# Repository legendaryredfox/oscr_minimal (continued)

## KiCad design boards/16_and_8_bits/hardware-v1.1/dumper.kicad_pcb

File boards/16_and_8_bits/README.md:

# 16_and_8_bits — placa de 5 slots

**README por versão** (renders de cima e de baixo, peças, diferenças): [v1.0](hardware-v1.0/README.md), [v1.1](hardware-v1.1/README.md).

**Slots:** SNES (62p), NES (72p), Famicom (60p), Mega Drive (64p) e GBA (32p, SMD, 3,3 V). Um cartucho por vez.

**Versões (regra do usuário: v1.0 = a mínima que funciona, com fusível; outras versões = mais recursos):**

- **v1.0** (144,1 × 118,1 mm): a mínima, com o fusível F1 (D144).
- **v1.1** (144,1 × 134,1 mm): a v1.0 mais o **seletor de tensão 3,3 V/5 V** nos slots **NES, Famicom e Mega Drive** (LDO LD1117V33 U4, Q1 de bypass, Q2 de comando pelo D18, R3 a R5, C10, C11) e o J1 "TRAVA 3,3 V" (D157, D138, D147). **O SNES fica sempre em 5 V** (o SA-1 não funciona a 3,3 V), assim como o PIC e o Si5351; o GBA tem o regulador U3. Firmware: ambiente `SerialASCII_Volt`.

**Estado:** DRC 0 erros nas duas versões (só os 4 avisos de biblioteca do furo M3), netlist confere com `docs/pinmap.md`, gerbers v1.0 e v1.1 em `fab/` (`fab/PEDIDO.md`). A v1.1 foi roteada pelo Freerouting: **revisar o layout no KiCad antes de encomendar**. Nada encomendado nem montado.

| Pasta | Conteúdo |
|---|---|
| `hardware-v1.0/`, `hardware-v1.1/` | `dumper.kicad_pro/_sch/_pcb` (KiCad 10) |
| `fab/` | `gerbers-<versão>/`, `bom-<versão>.csv`, `dumper-<versão>-jlcpcb.zip`, `PEDIDO.md` |
| `docs/` | `pinmap.md` (fonte da verdade), `bom.md`, `montagem.md` |

Verificação (da raiz do repositório):

```
python3 tools/check_netlist.py --board 16_and_8_bits boards/16_and_8_bits/hardware-v1.1/dumper.kicad_sch
kicad-cli sch erc boards/16_and_8_bits/hardware-v1.1/dumper.kicad_sch
kicad-cli pcb drc boards/16_and_8_bits/hardware-v1.1/dumper.kicad_pcb
tools/export_fab.sh 16_and_8_bits v1.1
```

**Peças opcionais:** o que se perde ao retirar cada componente, e que jogos são afetados, está em [`docs/bom.md`](docs/bom.md).

## Versões

Só a **v1.0** (`hardware-v1.0/`; fábrica em `fab/gerbers-v1.0/`, `fab/dumper-v1.0-jlcpcb.zip`, `fab/bom-v1.0.csv`; renders em `hardware-v1.0/render-cima.png` e `render-baixo.png`). Ela já leva o suporte do fusível F1 (D138). O 5V dos slots vai direto do Mega e **não é cortado por software** (o bloco de troca de cartucho, D126 a D128, foi retirado em D139): para trocar o cartucho, desligue o USB. Verificação: `python3 tools/check_netlist.py --board 16_and_8_bits`.

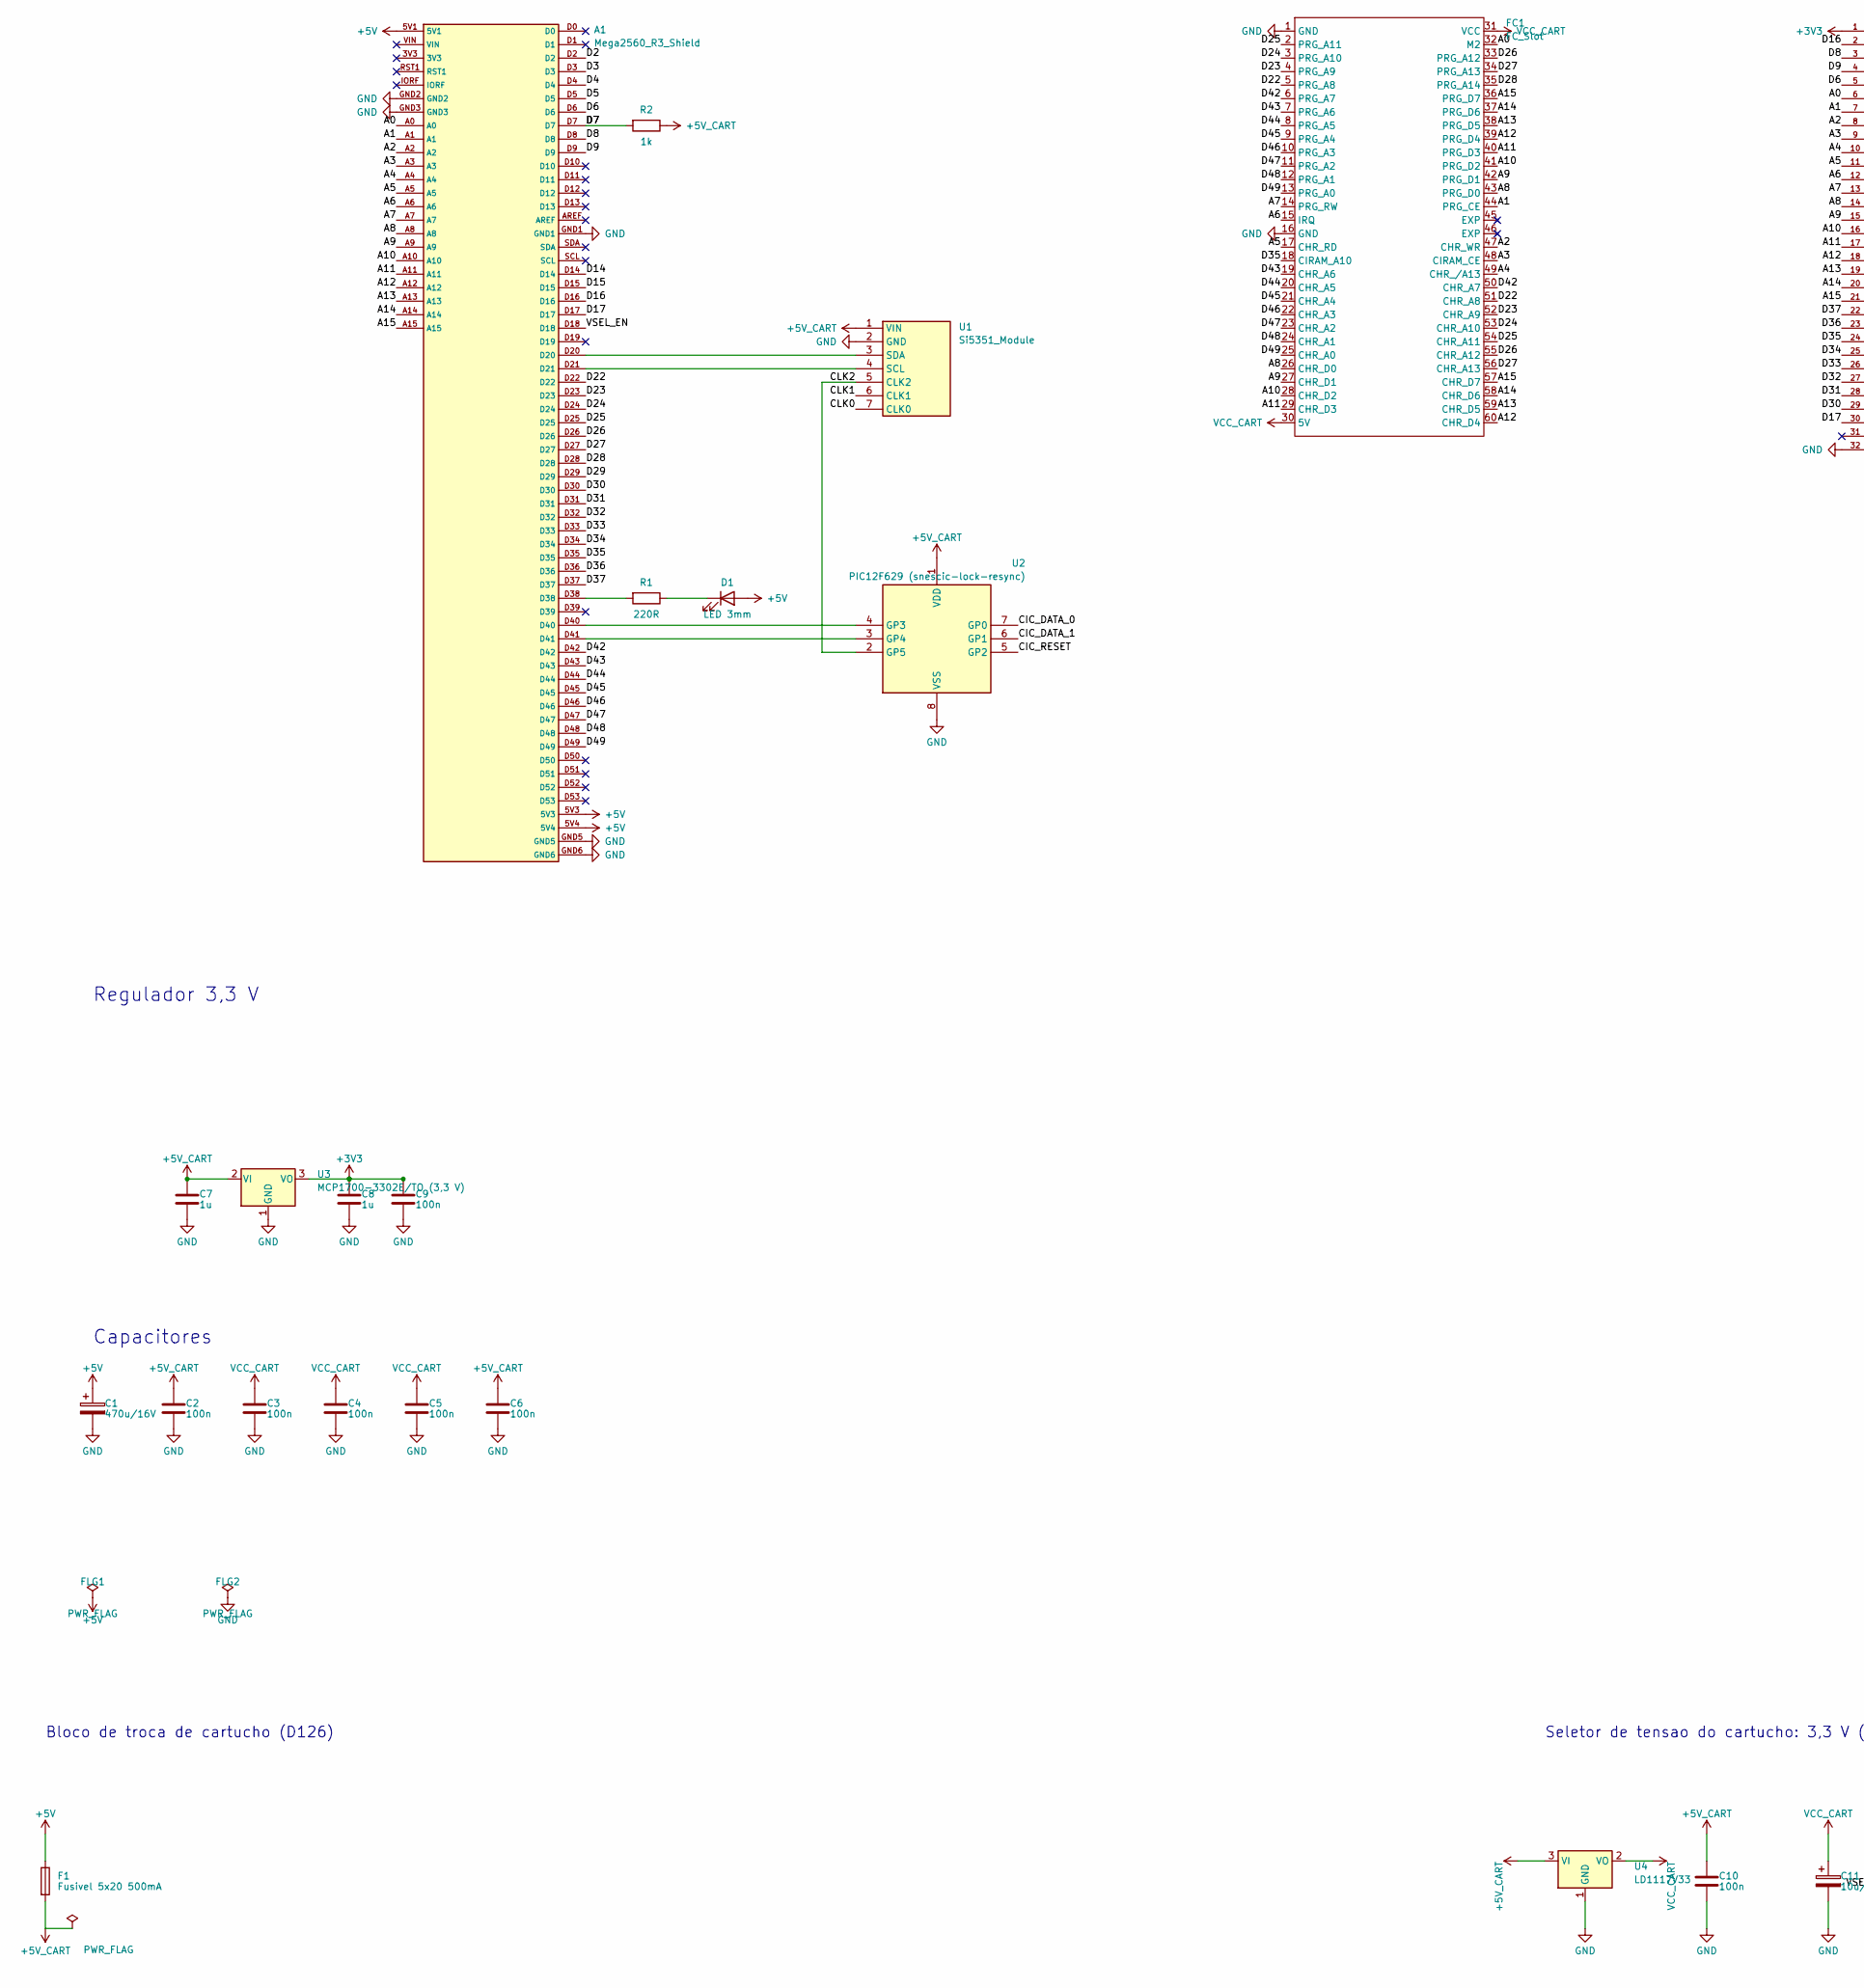
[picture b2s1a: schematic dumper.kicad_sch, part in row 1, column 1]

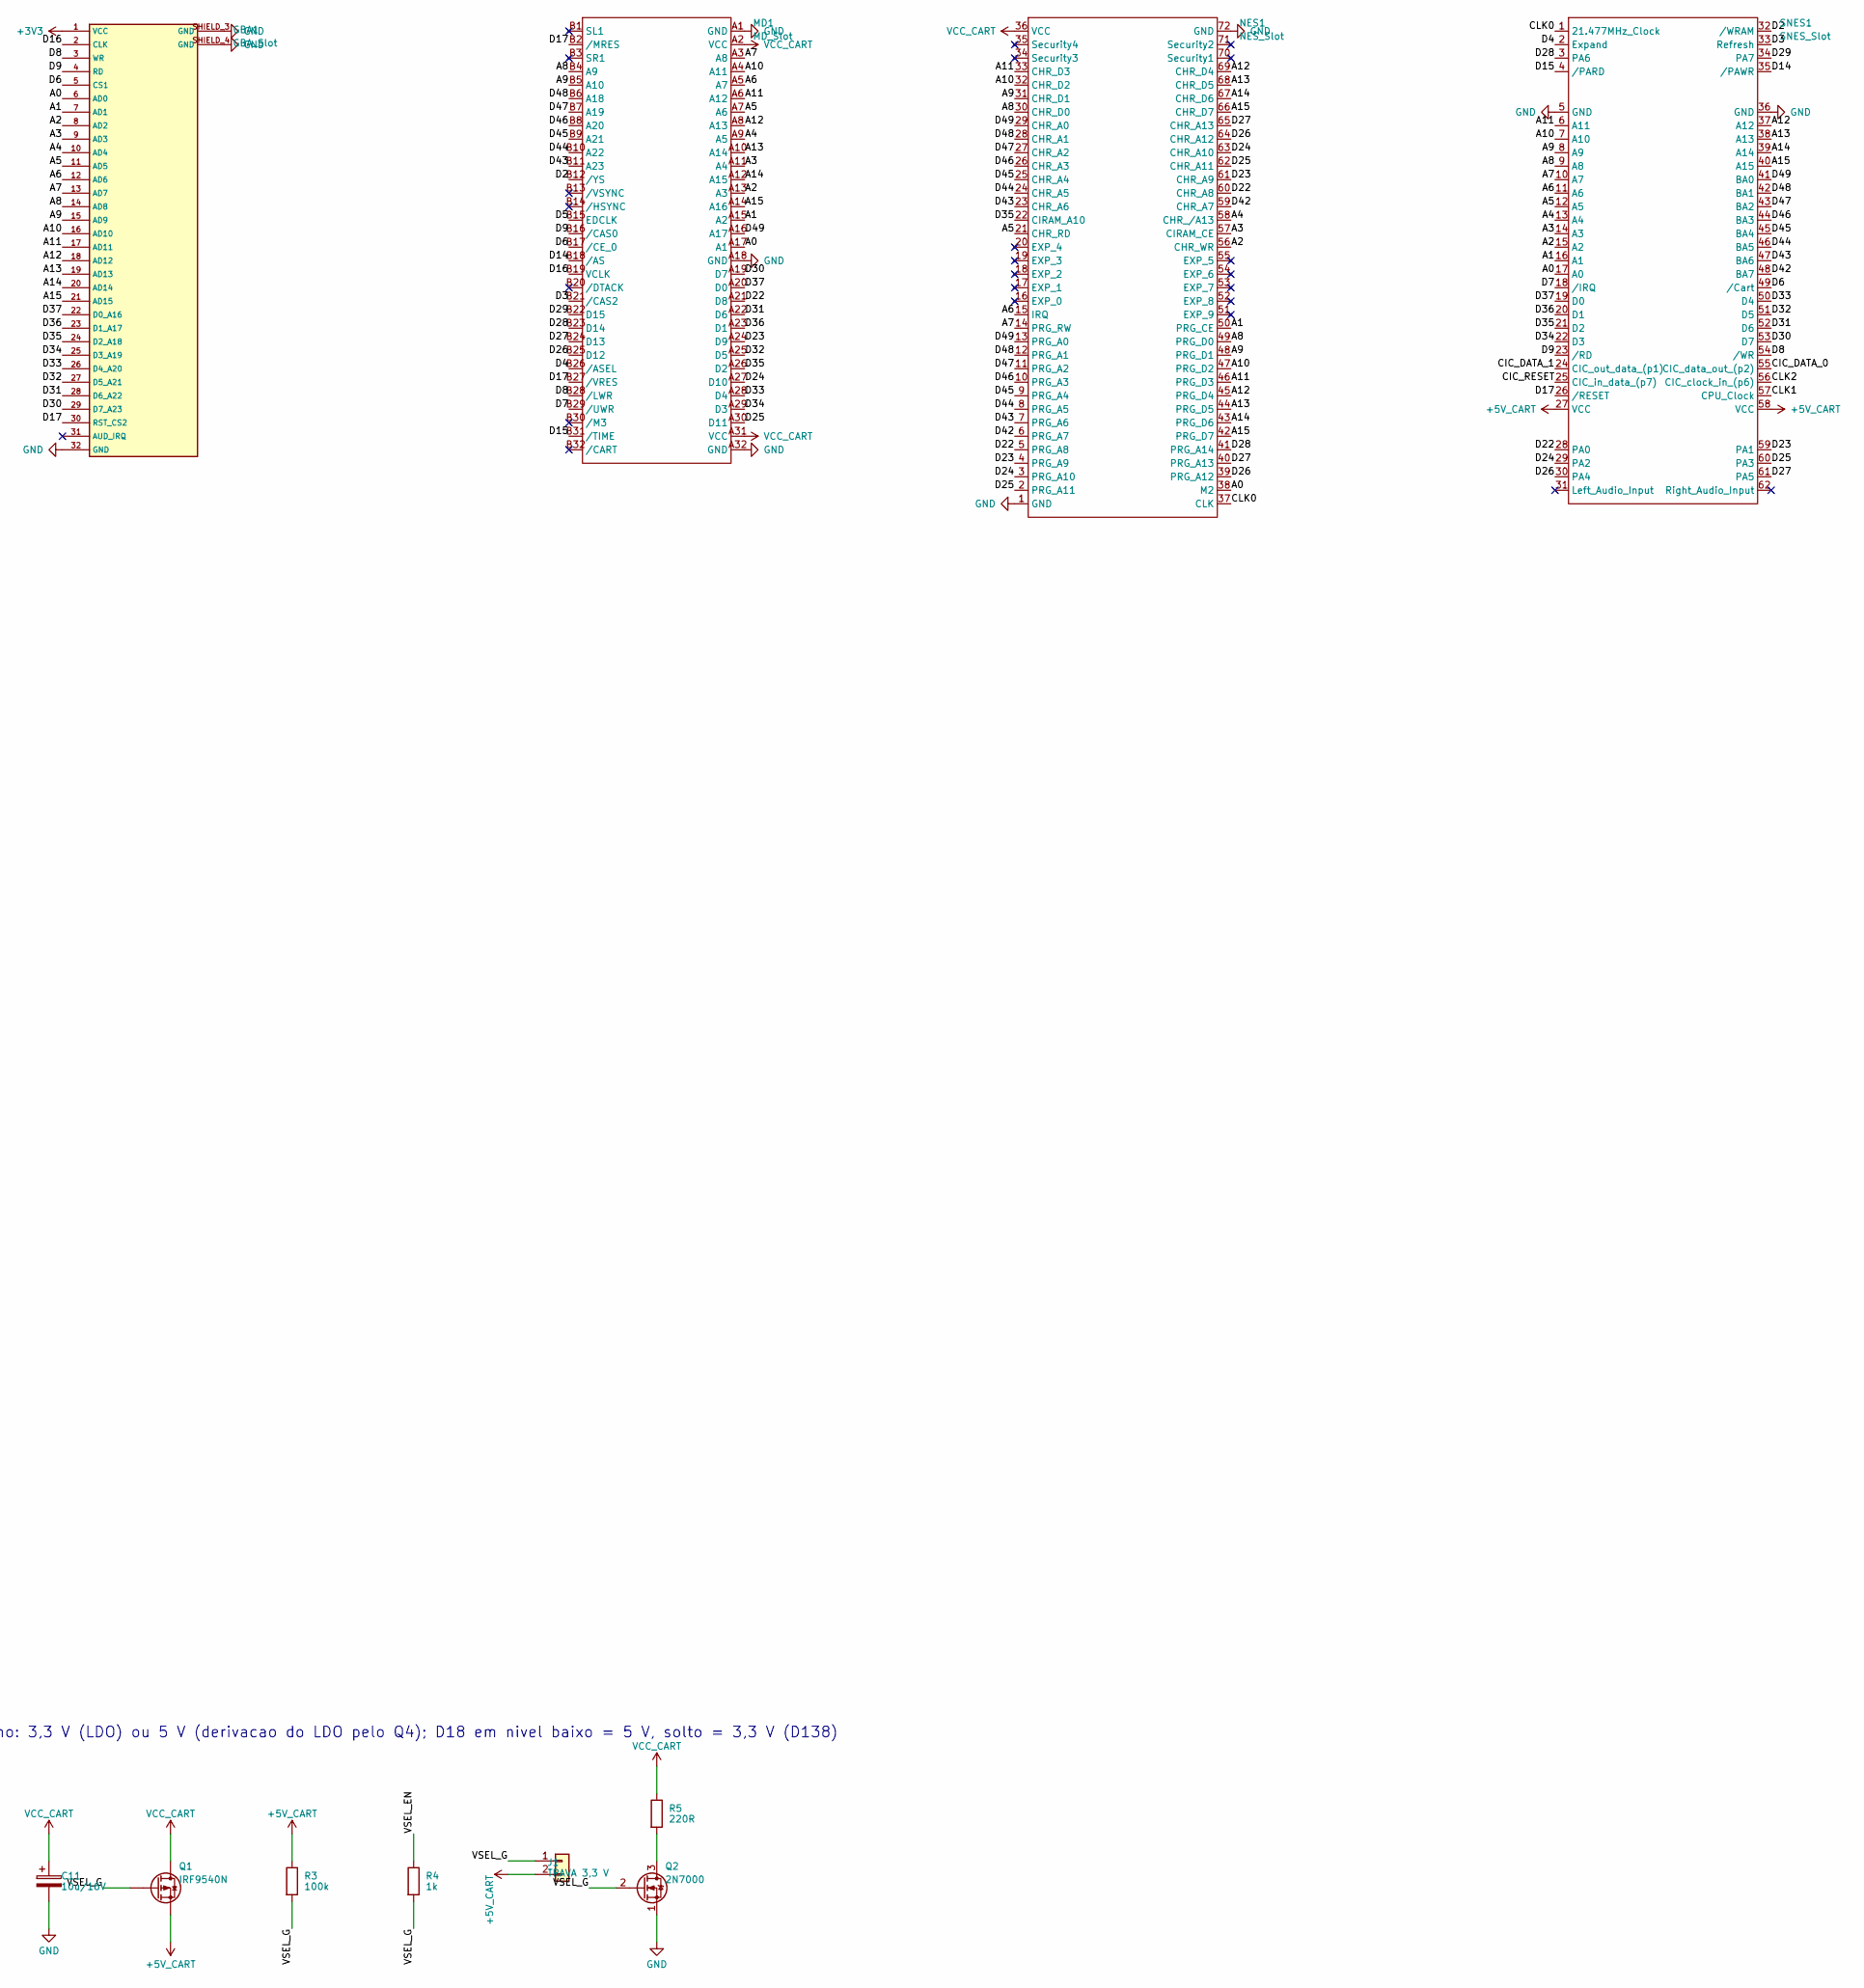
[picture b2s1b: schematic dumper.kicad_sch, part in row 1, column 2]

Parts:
A1: Mega2560_R3_Shield
C1: 470u/16V; CP_Radial_D8.0mm_P3.50mm
C2, C3, C4, C5, C6, C9, C10: 100n; C_Disc_D5.0mm_W2.5mm_P5.00mm
C7, C8: 1u; C_Disc_D5.0mm_W2.5mm_P5.00mm
C11: 10u/16V; CP_Radial_D5.0mm_P2.00mm
D1: LED 3mm; LED_D3.0mm
F1: Fusivel 5x20 500mA; Fuseholder_Littelfuse_100_series_5x20mm
FC1: FC_Slot
FLG1, FLG2, FLG3: PWR_FLAG
GBA1: GBA_Slot
J1: TRAVA 3,3 V; PinHeader_1x02_P2.54mm_Vertical
MD1: MD_Slot
NES1: NES_Slot
Q1: IRF9540N; TO-220-3_Vertical
Q2: 2N7000; TO-92_Inline
R1: 220R; R_Axial_DIN0207_L6.3mm_D2.5mm_P10.16mm_Horizontal
R2: 1k; R_Axial_DIN0207_L6.3mm_D2.5mm_P10.16mm_Horizontal
R3: 100k; R_Axial_DIN0204_L3.6mm_D1.6mm_P2.54mm_Vertical
R4: 1k; R_Axial_DIN0204_L3.6mm_D1.6mm_P2.54mm_Vertical
R5: 220R; R_Axial_DIN0204_L3.6mm_D1.6mm_P2.54mm_Vertical
SNES1: SNES_Slot
U1: Si5351_Module; PinSocket_1x07_P2.54mm_Vertical
U2: PIC12F629 (snescic-lock-resync); DIP-8_W7.62mm_Socket
U3: MCP1700-3302E/TO (3,3 V); TO-92
U4: LD1117V33; TO-220-3_Vertical

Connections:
+3V3: C8.1, C9.1, GBA1.1 (VCC), U3.3 (VO)
+5V: A1.5V1, A1.5V3, A1.5V4, C1.1, D1.2 (A), F1.1, FLG1.1
+5V_CART: C2.1, C6.1, C7.1, C10.1, F1.2, FLG3.1, J1.2, Q1.3 (S), R2.1, R3.1, SNES1.27 (VCC), SNES1.58 (VCC), U1.1 (VIN), U2.1 (VDD), U3.2 (VI), U4.3 (VI)
/A0: A1.A0, FC1.32 (M2), GBA1.6 (AD0), MD1.A17 (A1), NES1.38 (M2), SNES1.17 (A0)
/A1: A1.A1, FC1.44 (PRG_CE), GBA1.7 (AD1), MD1.A15 (A2), NES1.50 (PRG_CE), SNES1.16 (A1)
/A2: A1.A2, FC1.47 (CHR_WR), GBA1.8 (AD2), MD1.A13 (A3), NES1.56 (CHR_WR), SNES1.15 (A2)
/A3: A1.A3, FC1.48 (CIRAM_CE), GBA1.9 (AD3), MD1.A11 (A4), NES1.57 (CIRAM_CE), SNES1.14 (A3)
/A4: A1.A4, FC1.49 (CHR_/A13), GBA1.10 (AD4), MD1.A9 (A5), NES1.58 (CHR_/A13), SNES1.13 (A4)
/A5: A1.A5, FC1.17 (CHR_RD), GBA1.11 (AD5), MD1.A7 (A6), NES1.21 (CHR_RD), SNES1.12 (A5)
/A6: A1.A6, FC1.15 (IRQ), GBA1.12 (AD6), MD1.A5 (A7), NES1.15 (IRQ), SNES1.11 (A6)
/A7: A1.A7, FC1.14 (PRG_RW), GBA1.13 (AD7), MD1.A3 (A8), NES1.14 (PRG_RW), SNES1.10 (A7)
/A8: A1.A8, FC1.26 (CHR_D0), FC1.43 (PRG_D0), GBA1.14 (AD8), MD1.B4 (A9), NES1.30 (CHR_D0), NES1.49 (PRG_D0), SNES1.9 (A8)
/A9: A1.A9, FC1.27 (CHR_D1), FC1.42 (PRG_D1), GBA1.15 (AD9), MD1.B5 (A10), NES1.31 (CHR_D1), NES1.48 (PRG_D1), SNES1.8 (A9)
/A10: A1.A10, FC1.28 (CHR_D2), FC1.41 (PRG_D2), GBA1.16 (AD10), MD1.A4 (A11), NES1.32 (CHR_D2), NES1.47 (PRG_D2), SNES1.7 (A10)
/A11: A1.A11, FC1.29 (CHR_D3), FC1.40 (PRG_D3), GBA1.17 (AD11), MD1.A6 (A12), NES1.33 (CHR_D3), NES1.46 (PRG_D3), SNES1.6 (A11)
/A12: A1.A12, FC1.39 (PRG_D4), FC1.60 (CHR_D4), GBA1.18 (AD12), MD1.A8 (A13), NES1.45 (PRG_D4), NES1.69 (CHR_D4), SNES1.37 (A12)
/A13: A1.A13, FC1.38 (PRG_D5), FC1.59 (CHR_D5), GBA1.19 (AD13), MD1.A10 (A14), NES1.44 (PRG_D5), NES1.68 (CHR_D5), SNES1.38 (A13)
/A14: A1.A14, FC1.37 (PRG_D6), FC1.58 (CHR_D6), GBA1.20 (AD14), MD1.A12 (A15), NES1.43 (PRG_D6), NES1.67 (CHR_D6), SNES1.39 (A14)
/A15: A1.A15, FC1.36 (PRG_D7), FC1.57 (CHR_D7), GBA1.21 (AD15), MD1.A14 (A16), NES1.42 (PRG_D7), NES1.66 (CHR_D7), SNES1.40 (A15)
/CIC_DATA_0: SNES1.55 (CIC_data_out_(p2)), U2.7 (GP0)
/CIC_DATA_1: SNES1.24 (CIC_out_data_(p1)), U2.6 (GP1)
/CIC_RESET: SNES1.25 (CIC_in_data_(p7)), U2.5 (GP2)
/CLK0: NES1.37 (CLK), SNES1.1 (21.477MHz_Clock), U1.7 (CLK0)
/CLK1: SNES1.57 (CPU_Clock), U1.6 (CLK1)
/CLK2: SNES1.56 (CIC_clock_in_(p6)), U1.5 (CLK2), U2.2 (GP5)
/D2: A1.D2, MD1.B12 (/YS), SNES1.32 (/WRAM)
/D3: A1.D3, MD1.B21 (/CAS2), SNES1.33 (Refresh)
/D4: A1.D4, MD1.B26 (/ASEL), SNES1.2 (Expand)
/D5: A1.D5, MD1.B15 (EDCLK)
/D6: A1.D6, GBA1.5 (CS1), MD1.B17 (/CE_0), SNES1.49 (/Cart)
/D7: A1.D7, MD1.B29 (/UWR), R2.2, SNES1.18 (/IRQ)
/D8: A1.D8, GBA1.3 (WR), MD1.B28 (/LWR), SNES1.54 (/WR)
/D9: A1.D9, GBA1.4 (RD), MD1.B16 (/CAS0), SNES1.23 (/RD)
/D14: A1.D14, MD1.B18 (/AS), SNES1.35 (/PAWR)
/D15: A1.D15, MD1.B31 (/TIME), SNES1.4 (/PARD)
/D16: A1.D16, GBA1.2 (CLK), MD1.B19 (VCLK)
/D17: A1.D17, GBA1.30 (RST_CS2), MD1.B2 (/MRES), MD1.B27 (/VRES), SNES1.26 (/RESET)
/D22: A1.D22, FC1.5 (PRG_A8), FC1.51 (CHR_A8), MD1.A21 (D8), NES1.5 (PRG_A8), NES1.60 (CHR_A8), SNES1.28 (PA0)
/D23: A1.D23, FC1.4 (PRG_A9), FC1.52 (CHR_A9), MD1.A24 (D9), NES1.4 (PRG_A9), NES1.61 (CHR_A9), SNES1.59 (PA1)
/D24: A1.D24, FC1.3 (PRG_A10), FC1.53 (CHR_A10), MD1.A27 (D10), NES1.3 (PRG_A10), NES1.63 (CHR_A10), SNES1.29 (PA2)
/D25: A1.D25, FC1.2 (PRG_A11), FC1.54 (CHR_A11), MD1.A30 (D11), NES1.2 (PRG_A11), NES1.62 (CHR_A11), SNES1.60 (PA3)
/D26: A1.D26, FC1.33 (PRG_A12), FC1.55 (CHR_A12), MD1.B25 (D12), NES1.39 (PRG_A12), NES1.64 (CHR_A12), SNES1.30 (PA4)
/D27: A1.D27, FC1.34 (PRG_A13), FC1.56 (CHR_A13), MD1.B24 (D13), NES1.40 (PRG_A13), NES1.65 (CHR_A13), SNES1.61 (PA5)
/D28: A1.D28, FC1.35 (PRG_A14), MD1.B23 (D14), NES1.41 (PRG_A14), SNES1.3 (PA6)
/D29: A1.D29, MD1.B22 (D15), SNES1.34 (PA7)
/D30: A1.D30, GBA1.29 (D7_A23), MD1.A19 (D7), SNES1.53 (D7)
/D31: A1.D31, GBA1.28 (D6_A22), MD1.A22 (D6), SNES1.52 (D6)
/D32: A1.D32, GBA1.27 (D5_A21), MD1.A25 (D5), SNES1.51 (D5)
/D33: A1.D33, GBA1.26 (D4_A20), MD1.A28 (D4), SNES1.50 (D4)
/D34: A1.D34, GBA1.25 (D3_A19), MD1.A29 (D3), SNES1.22 (D3)
/D35: A1.D35, FC1.18 (CIRAM_A10), GBA1.24 (D2_A18), MD1.A26 (D2), NES1.22 (CIRAM_A10), SNES1.21 (D2)
/D36: A1.D36, GBA1.23 (D1_A17), MD1.A23 (D1), SNES1.20 (D1)
/D37: A1.D37, GBA1.22 (D0_A16), MD1.A20 (D0), SNES1.19 (D0)
/D42: A1.D42, FC1.6 (PRG_A7), FC1.50 (CHR_A7), NES1.6 (PRG_A7), NES1.59 (CHR_A7), SNES1.48 (BA7)
/D43: A1.D43, FC1.7 (PRG_A6), FC1.19 (CHR_A6), MD1.B11 (A23), NES1.7 (PRG_A6), NES1.23 (CHR_A6), SNES1.47 (BA6)
/D44: A1.D44, FC1.8 (PRG_A5), FC1.20 (CHR_A5), MD1.B10 (A22), NES1.8 (PRG_A5), NES1.24 (CHR_A5), SNES1.46 (BA5)
/D45: A1.D45, FC1.9 (PRG_A4), FC1.21 (CHR_A4), MD1.B9 (A21), NES1.9 (PRG_A4), NES1.25 (CHR_A4), SNES1.45 (BA4)
/D46: A1.D46, FC1.10 (PRG_A3), FC1.22 (CHR_A3), MD1.B8 (A20), NES1.10 (PRG_A3), NES1.26 (CHR_A3), SNES1.44 (BA3)
/D47: A1.D47, FC1.11 (PRG_A2), FC1.23 (CHR_A2), MD1.B7 (A19), NES1.11 (PRG_A2), NES1.27 (CHR_A2), SNES1.43 (BA2)
/D48: A1.D48, FC1.12 (PRG_A1), FC1.24 (CHR_A1), MD1.B6 (A18), NES1.12 (PRG_A1), NES1.28 (CHR_A1), SNES1.42 (BA1)
/D49: A1.D49, FC1.13 (PRG_A0), FC1.25 (CHR_A0), MD1.A16 (A17), NES1.13 (PRG_A0), NES1.29 (CHR_A0), SNES1.41 (BA0)
/VSEL_EN: A1.D18, R4.1
/VSEL_G: J1.1, Q1.1 (G), Q2.2 (G), R3.2, R4.2
GND: A1.GND1, A1.GND2, A1.GND3, A1.GND5, A1.GND6, C1.2, C2.2, C3.2, C4.2, C5.2, C6.2, C7.2, C8.2, C9.2, C10.2, C11.2, FC1.1 (GND), FC1.16 (GND), FLG2.1, GBA1.32 (GND), GBA1.SHIELD_3 (GND), GBA1.SHIELD_4 (GND), MD1.A1 (GND), MD1.A18 (GND), MD1.A32 (GND), NES1.1 (GND), NES1.72 (GND), Q2.1 (S), SNES1.5 (GND), SNES1.36 (GND), U1.2 (GND), U2.8 (VSS), U3.1 (GND), U4.1 (GND)
unnamed: A1.D38, R1.2
unnamed: D1.1 (K), R1.1
unnamed: Q2.3 (D), R5.2
unnamed: A1.D21, U1.4 (SCL)
unnamed: A1.D20, U1.3 (SDA)
unnamed: A1.D40, U2.4 (GP3)
unnamed: A1.D41, U2.3 (GP4)
VCC_CART: C3.1, C4.1, C5.1, C11.1, FC1.30 (5V), FC1.31 (VCC), MD1.A2 (VCC), MD1.A31 (VCC), NES1.36 (VCC), Q1.2 (D), R5.1, U4.2 (VO)

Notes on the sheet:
Regulador 3,3 V
Capacitores
Bloco de troca de cartucho (D126)
Seletor de tensao do cartucho: 3,3 V (LDO) ou 5 V (derivacao do LDO pelo Q4); D18 em nivel baixo = 5 V, solto = 3,3 V (D138)

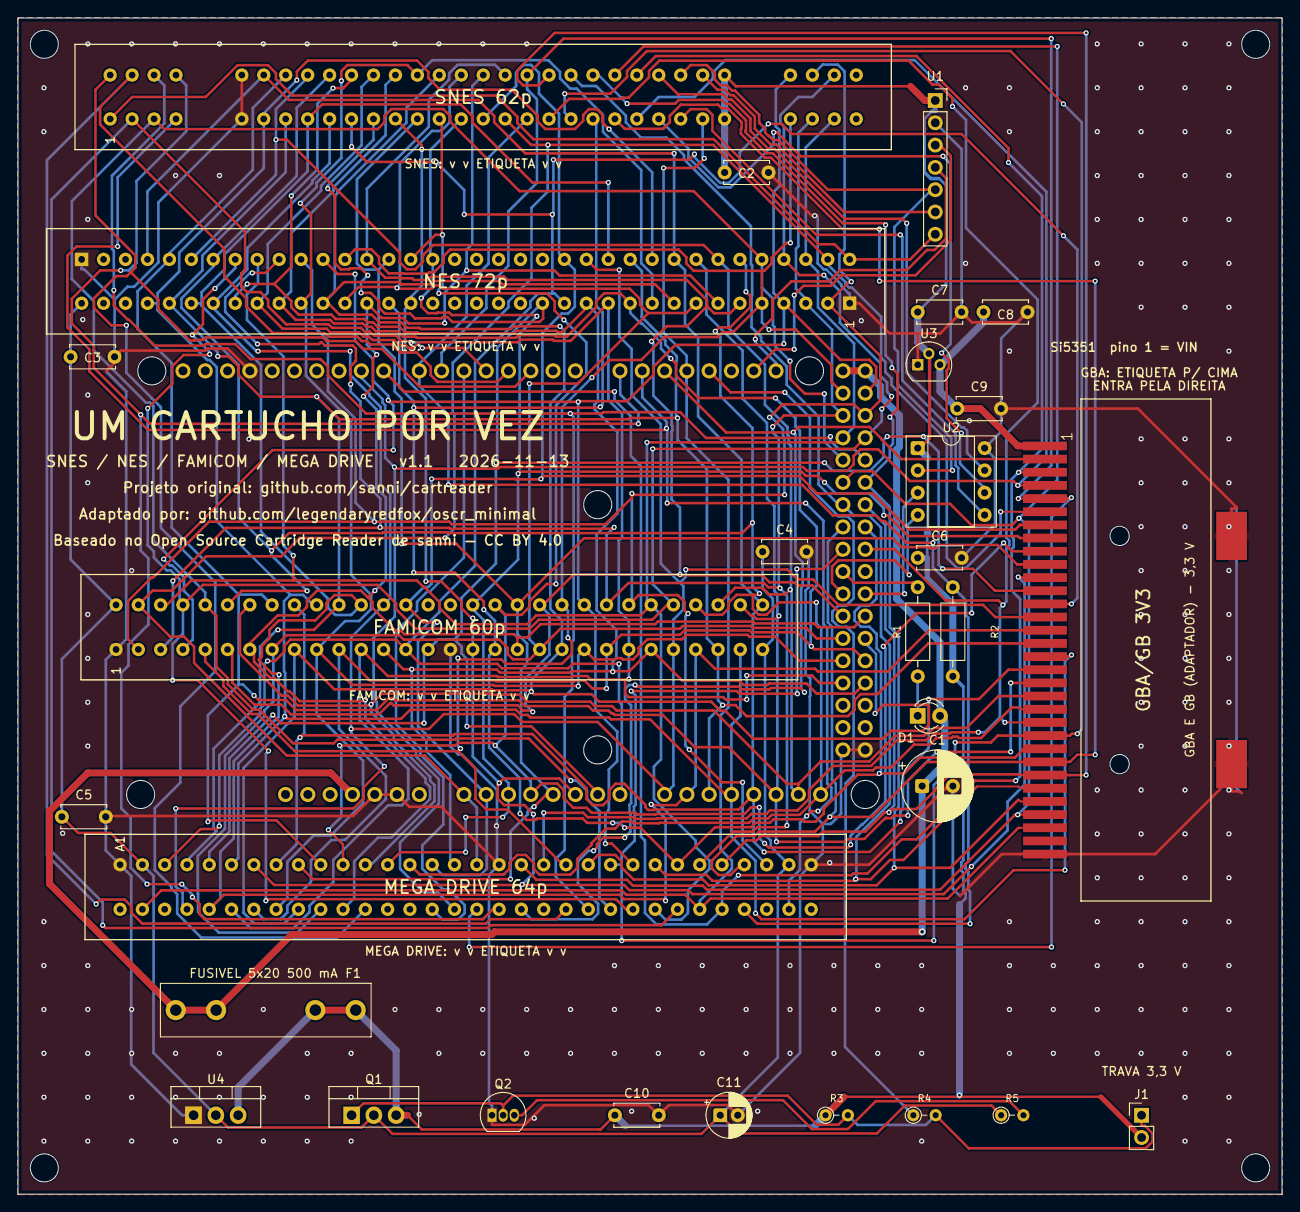
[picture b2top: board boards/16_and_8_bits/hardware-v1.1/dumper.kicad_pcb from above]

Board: 2 copper layers, 144.0 x 134.0 mm, 35 parts (0 on the bottom side), 72 nets.

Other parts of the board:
MH1, MH2, MH3, MH4: MountingHole_3.2mm; MountingHole_3.2mm_M3

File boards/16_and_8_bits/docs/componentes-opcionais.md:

# 16_and_8_bits — componentes que podem ser retirados e o que se perde

Placa de 5 slots v1.0: SNES, NES, Famicom, Mega Drive e GBA (`boards/16_and_8_bits/`). Sem chave de 5 V (Q1) nem proteção das linhas. Um cartucho por vez.

> **Nada aqui foi testado em hardware.** Fontes: `docs/bom.md`, `pinmap.md`, firmware, D54 e `docs/referencia/limites-gb.md`.

| Peça | Retirar? | O que deixa de funcionar | Jogos afetados |
|---|---|---|---|
| **U2** PIC12F629 (CIC) + soquete | **Perde o SA-1** | O PIC emula o CIC do SNES; o SA-1 só responde com ele rodando | Só **SA-1** (Super Mario RPG, Kirby Super Star, Kirby's Dream Land 3, Jikkyou Oshaberi Parodius, Dragon Ball Z: Hyper Dimension e outros; lista não exaustiva em `snes/docs/componentes-opcionais.md`). NES, Famicom, Mega Drive e GBA não usam |
| **U1** módulo Si5351 | **Perde o SA-1**; o PIC fica sem clock | SNES: clock mestre (pino 1), CPU (57) e CIC (56). NES: o `CLK0` vai ao pino 37, mas o firmware atual não o usa | SA-1; futuros Satellaview e SF Memory. NES: nenhum conhecido |
| **R2** 1 kΩ (pull-up de D7, `/IRQ` do SNES) | Sim, com cuidado | `/IRQ` solta. D7 também é o `/UWR` do Mega Drive (pino B29); o pull-up estava no HW5 | Nenhum conhecido. Inferência |
| **U3** MCP1700-3302E + **C7**, **C8** (1 µF) + **C9** | **Perde o GBA, o GB e o GBC** | O slot GBA só tem 3,3 V, vindo do U3. Sem ele, sem energia no slot. Nunca ligar o GBA ao 5 V | Todos os GBA, GB e GBC. SNES, NES, Famicom e Mega Drive não dependem (5 V direto) |
| **D1** LED + **R1** 220 Ω | Sim | Indicação de atividade | Nenhum |
| **C2** SNES, **C3** NES, **C4** Famicom, **C5** Mega Drive, **C9** GBA, **C6** PIC (100 nF) | Não recomendado | Desacoplamento do slot ou do PIC. Sem eles, leitura errada possível (CRC variável) | Mais provável: SA-1, ROM grande (SSF2), GBA com Flash. Inferência |
| **C1** 470 µF | Não recomendado | Reserva do 5 V | Todos |

## Montagens parciais

Como os slots dividem os mesmos barramentos, pode-se montar só os slots que o usuário vai usar; os demais ficam vazios sem prejuízo, **menos** o desacoplamento de cada slot (montar o capacitor do slot usado). Sem PIC e sem Si5351 a placa lê tudo menos SA-1. Sem U3 e seus capacitores perde-se tudo do GBA (inclusive GB/GBC por adaptador), mas o slot GBA pode continuar vazio.

Sobre GB/GBC a 3,3 V: ver `docs/referencia/limites-gb.md` (alguns GB antigos podem falhar; jumper para 5 V só para GB/GBC, nunca GBA).

## F1, J1 e seletor de tensão (D138)

<!-- d138 -->

| Peça | Opcional? | O que se perde sem ela |
|---|---|---|
| F1 (suporte e fusível 5×20 mm, 500 mA) | **Sim**, mas sem o fusível no suporte a placa não tem 5 V (um fio no lugar dele também serve) | só a proteção contra curto no cartucho (placa, Mega e USB) |

**F1**: fusível de vidro **5×20 mm, 500 mA, ação rápida**, em suporte de clipes de furo passante (Littelfuse série 100 ou equivalente): o fusível queimado se troca **sem solda**. Fica em série com o 5 V que a placa recebe do Mega. Queda de 0,1 a 0,2 V a 200 mA. Vale para as versões v1.0 (exceção declarada à regra "a v1.0 é a mais barata que funciona", D138). **Sem o fusível no suporte, a placa fica sem 5 V**: use um fusível de 500 mA (ou um pedaço de fio na falta) e confira o valor ao trocar.

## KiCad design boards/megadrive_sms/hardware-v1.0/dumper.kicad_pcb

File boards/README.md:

# boards/ — variantes de hardware

Cada pasta é uma versão mínima de hardware do OSCR, em shield para Arduino Mega 2560 R3, só USB (sem LCD, SD e RTC). Firmware, `host/` e `gui/` (raiz) são comuns; o que muda entre as placas são os slots e a pinagem.

| Pasta | Slots | Estado |
|---|---|---|
| [`16_bits/`](16_bits/) | SNES, Mega Drive | Projeto KiCad derivado da `16_and_8_bits`, 108 × 86 mm. **Versões v1.0, v1.2 (sem TVS) e v1.3 (seletor de tensão, sem TVS nem resistores de 470 Ω), D128, D139 e D140.** Gerbers v. 1.2 (D87: `/CART` no D50, C5 e C6, pontos de teste a 2,54 mm, D99) e v1.0 (a antiga `rev2`: alimentação em 0,8 mm, D97; o zip da v1.0 original, com trilhas de 0,3 mm, saiu do repositório em D110) |
| [`megadrive/`](megadrive/) | Mega Drive | Projeto KiCad criado de `16_bits` (D92), slot no centro, 107 × 65 mm, gerbers v1.1 gerados. **v1.1 com o seletor de tensão 3,3 V/5 V (D138).** Nada encomendado |
| [`snes/`](snes/) | SNES | Projeto KiCad criado de `16_bits` (D93), PIC12F629 em soquete, 107 × 65 mm, só a v1.0 (o SA-1 precisa de 5 V: sem seletor). Nada encomendado |
| [`nes/`](nes/) | NES | Projeto KiCad criado da `16_and_8_bits` (D95), Si5351 sem PIC, 110 × 65 mm, gerbers v1.1 gerados. Famicom em `famicom/` ou `famicom_nes/`. **v1.1 com o seletor de tensão 3,3 V/5 V (D138).** Nada encomendado |
| [`famicom/`](famicom/) | Famicom | Projeto KiCad criado da `16_and_8_bits` (D98), sem Si5351 nem PIC, 107 × 65 mm, gerbers v1.1 gerados. **v1.1 com o seletor de tensão 3,3 V/5 V (D138).** Nada encomendado |
| [`famicom_nes/`](famicom_nes/) | Famicom e NES | Projeto KiCad criado da `16_and_8_bits` (D100), Si5351 sem PIC, 117 × 79 mm (D124), gerbers v1.1 gerados. **v1.1 com o seletor de tensão 3,3 V/5 V (D138).** Nada encomendado |
| [`16_and_8_bits/`](16_and_8_bits/) | SNES, NES, Famicom, Mega Drive, GBA | Projeto KiCad pronto, 144 × 118 mm (v1.0, mínima com fusível) e 144 × 134 mm (**v1.1 com o seletor de tensão 3,3 V/5 V nos slots NES, Famicom e Mega Drive**, D157). Nada encomendado |
| [`megadrive_sms/`](megadrive_sms/) | Mega Drive, Master System | Projeto KiCad criado da `megadrive` v1.0 (D136), 107,1 × 83,1 mm, **v1.0 sem o bloco de troca**, gerbers v1.0 gerados. Nada encomendado. Pendências: direção da etiqueta do SMS, núcleo SMS no firmware |
| [`8_bits/`](8_bits/) | NES, Famicom, Master System | Projeto KiCad criado da `famicom_nes` com o slot SMS da `megadrive_sms` (D153), 117,1 × 97,1 mm (v1.0, mínima com fusível) e 117,1 × 109,1 mm (v1.1, com o seletor de tensão). Nada encomendado |
| [`gb_gba/`](gb_gba/) | GBA; GB e GBC por adaptador | Projeto KiCad criado de `16_and_8_bits` (D94), 138 × 67 mm, gerbers v1.0 gerados. Nada encomendado |
| [`n64/`](n64/) | N64 | Projeto KiCad criado da `16_and_8_bits` (D121), 3,3 V, Si5351 só para a EEPROM, 110,1 × 65,1 mm, só a v1.0 (placa de 3,3 V: sem seletor). Nada encomendado |
| [`completa/`](completa/) | SNES, NES, Famicom, Mega Drive, Master System, N64 e GBA | Projeto KiCad criado da `16_and_8_bits` com os slots SMS e N64 acrescentados (D156), 144,2 × 152,2 mm (v1.0, mínima com fusível) e 144,2 × 168,2 mm (v1.1, com o seletor de tensão nos slots de 5 V, menos o SNES). O N64 está desligado no firmware. Nada encomendado |
| [`_lib/`](_lib/) | Símbolos e footprints compartilhados | Em uso por todas as placas com projeto KiCad |

Cada placa com projeto tem um `render.png` (render 3D do KiCad, vista de cima, da versão mais nova) e, **dentro da pasta de cada versão** (`hardware-v1.0/` etc.), `render-cima.png` e `render-baixo.png` (1768 × 1064, print do render 3D do KiCad) ao lado do `README.md` da versão; refazer com `tools/render_board.sh <placa> <versões...>` e `docs/bom.md`: peças que podem ficar sem montar, o que deixa de funcionar e quais cartuchos são afetados.

## Troca de cartucho, F1 e seletor de tensão (D138, D139)

O 5V dos slots **não é cortado por software** em nenhuma placa: o bloco de troca de cartucho (Q1, Q2, Q3, LEDs verde e amarelo, D19 e D53; D126 a D128) foi retirado em D139. Para trocar o cartucho, **desligue o USB**. Ficaram o F1 (suporte de fusível 5×20 mm de 500 mA, em todas as versões), e nas v1.1 com slot de 5 V o seletor 3,3 V/5 V, o jumper J1 "TRAVA 3,3 V" e os resistores de 470 Ω em série. Circuito e peças: [`docs/referencia/seletor-tensao.md`](../docs/referencia/seletor-tensao.md).

## Como os esquemáticos são desenhados

Para leitura humana (D122): os circuitos locais (LED, resistores, capacitores, Si5351, PIC, regulador, pull-ups) têm **fios diretos** entre os pinos; a alimentação usa **símbolos** `+5V`, `+3V3`, `+5V_CART` e `GND`; **rótulos de net só nos barramentos longos** entre o Mega e os slots. As folhas são geradas por `tools/sch/regen.py` (preserva peças, referências e UUIDs, só refaz o desenho); `tools/sch/verify.py` confere que a conectividade ficou idêntica e `tools/sch/sync_names.py` alinha os nomes de net do PCB (a geometria não muda).

## Layout de cada variante

```
boards/<variante>/
├── README.md        # slots, estado, decisões próprias
├── hardware-v1.0/   # uma pasta por versão (hardware-v1.1/ ...): projeto KiCad (dumper.kicad_pro/_sch/_pcb, fp-lib-table, sym-lib-table) e README.md da versão
├── fab/             # por versão: gerbers-<versão>/, bom-<versão>.csv e dumper-<versão>-jlcpcb.zip
└── docs/            # pinmap.md, bom.md, montagem.md da variante
```

As tabelas de bibliotecas apontam para `${KIPRJMOD}/../../_lib/`. Pinagem idêntica ao OSCR HW5 continua regra de ouro (`CLAUDE.md`, seção 3). Uma variante nova nasce copiando o esqueleto e gerando o próprio `docs/pinmap.md`; `tools/check_netlist.py` aceita `--board <pasta>` e `tools/export_fab.sh <pasta> <versão>` gera os arquivos da fábrica; `gen_pinmap.py` e os demais scripts gerais de `tools/` apontam para `16_and_8_bits/`. As placas de um sistema só têm scripts próprios em `tools/boards/<placa>/` (receita completa em `boards/nes/README.md` e na D96).

Todas as placas novas (`megadrive`, `snes`, `nes`, `famicom`, `famicom_nes`, `gb_gba`, `n64`) e as v1.1 foram roteadas por autoroteador (na v1.1, o roteamento inteiro foi refeito) e **não foram revisadas à mão no KiCad**; nenhuma foi encomendada, montada ou testada com cartucho.

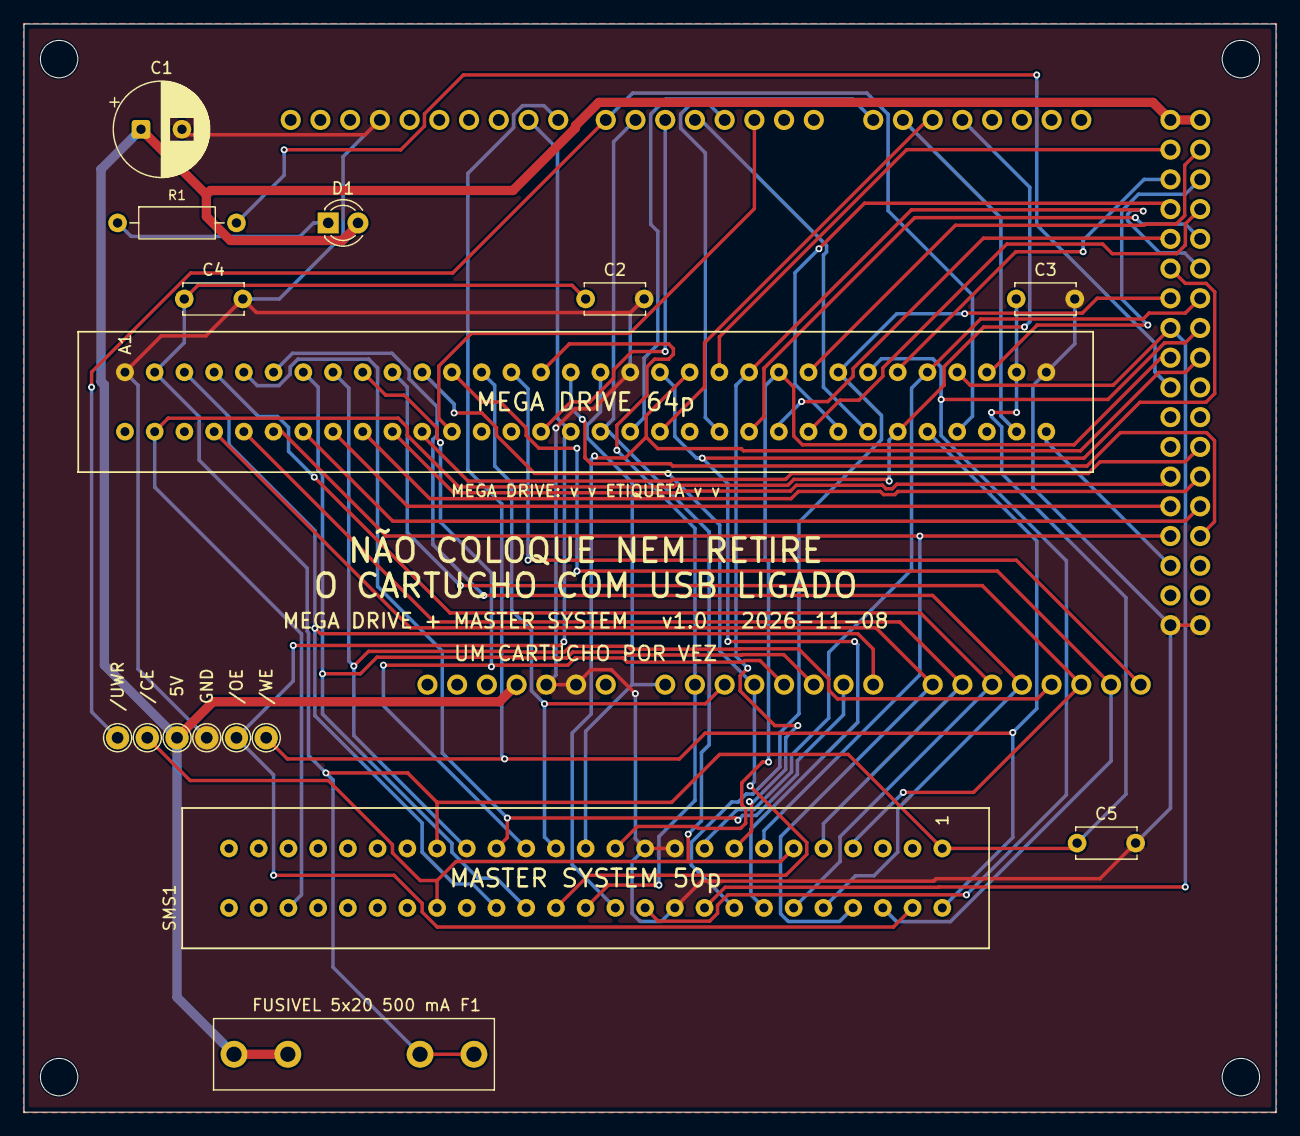
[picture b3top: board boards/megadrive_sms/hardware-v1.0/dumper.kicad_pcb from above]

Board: 2 copper layers, 107.0 x 93.0 mm, 21 parts (0 on the bottom side), 57 nets.

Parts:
A1: Mega2560_R3_Shield
C1: 470u/16V; CP_Radial_D8.0mm_P3.50mm
C2, C3, C4, C5: 100n; C_Disc_D5.0mm_W2.5mm_P5.00mm
D1: LED 3mm; LED_D3.0mm
F1: Fusivel 5x20 500mA; Fuseholder_Littelfuse_100_series_5x20mm
MD1: MD_Slot
MH1, MH2, MH5, MH6: MountingHole_3.2mm; MountingHole_3.2mm_M3
R1: 220R; R_Axial_DIN0207_L6.3mm_D2.5mm_P10.16mm_Horizontal
SMS1: SMS_Slot
TP1: 5V; TestPoint_THTPad_D2.0mm_Drill1.0mm
TP2: GND; TestPoint_THTPad_D2.0mm_Drill1.0mm
TP3: /CE; TestPoint_THTPad_D2.0mm_Drill1.0mm
TP4: /OE; TestPoint_THTPad_D2.0mm_Drill1.0mm
TP5: /WE; TestPoint_THTPad_D2.0mm_Drill1.0mm
TP6: /UWR; TestPoint_THTPad_D2.0mm_Drill1.0mm

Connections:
+5V: A1.5V1, A1.5V3, A1.5V4, C1.1, D1.2, F1.1, TP1.1
+5V_CART: C2.1, C3.1, C4.1, C5.1, F1.2, MD1.A2, MD1.A31, SMS1.1, SMS1.35
/A0: A1.A0, MD1.A17, SMS1.25
/A1: A1.A1, MD1.A15, SMS1.26
/A2: A1.A2, MD1.A13, SMS1.27
/A3: A1.A3, MD1.A11, SMS1.28
/A4: A1.A4, MD1.A9, SMS1.29
/A5: A1.A5, MD1.A7, SMS1.30
/A6: A1.A6, MD1.A5, SMS1.31
/A7: A1.A7, MD1.A3, SMS1.32
/A8: A1.A8, MD1.B4, SMS1.8
/A9: A1.A9, MD1.B5, SMS1.9
/A10: A1.A10, MD1.A4, SMS1.12
/A11: A1.A11, MD1.A6, SMS1.10
/A12: A1.A12, MD1.A8, SMS1.33
/A13: A1.A13, MD1.A10, SMS1.7
/A14: A1.A14, MD1.A12, SMS1.6
/A15: A1.A15, MD1.A14
/CART: A1.D50, MD1.B32
/D2: A1.D2, MD1.B12
/D3: A1.D3, MD1.B21
/D4: A1.D4, MD1.B26
/D5: A1.D5, MD1.B15
/D6: A1.D6, MD1.B17, SMS1.11, SMS1.36, TP3.1
/D7: A1.D7, MD1.B29, TP6.1
/D8: A1.D8, MD1.B28, SMS1.2, TP5.1
/D9: A1.D9, MD1.B16, SMS1.4, TP4.1
/D14: A1.D14, MD1.B18
/D15: A1.D15, MD1.B31
/D16: A1.D16, MD1.B19
/D17: A1.D17, MD1.B2, MD1.B27, SMS1.46
/D22: A1.D22, MD1.A21
/D23: A1.D23, MD1.A24
/D24: A1.D24, MD1.A27
/D25: A1.D25, MD1.A30
/D26: A1.D26, MD1.B25
/D27: A1.D27, MD1.B24
/D28: A1.D28, MD1.B23
/D29: A1.D29, MD1.B22
/D30: A1.D30, MD1.A19, SMS1.14
/D31: A1.D31, MD1.A22, SMS1.15
/D32: A1.D32, MD1.A25, SMS1.16
/D33: A1.D33, MD1.A28, SMS1.17
/D34: A1.D34, MD1.A29, SMS1.18
/D35: A1.D35, MD1.A26, SMS1.22
/D36: A1.D36, MD1.A23, SMS1.23
/D37: A1.D37, MD1.A20, SMS1.24
/D43: A1.D43, MD1.B11
/D44: A1.D44, MD1.B10
/D45: A1.D45, MD1.B9
/D46: A1.D46, MD1.B8
/D47: A1.D47, MD1.B7
/D48: A1.D48, MD1.B6, SMS1.13
/D49: A1.D49, MD1.A16
GND: A1.GND1, A1.GND2, A1.GND3, A1.GND5, A1.GND6, C1.2, C2.2, C3.2, C4.2, C5.2, MD1.A1, MD1.A18, MD1.A32, SMS1.19, SMS1.20, SMS1.21, TP2.1
unnamed: A1.D38, R1.2
unnamed: D1.1, R1.1
